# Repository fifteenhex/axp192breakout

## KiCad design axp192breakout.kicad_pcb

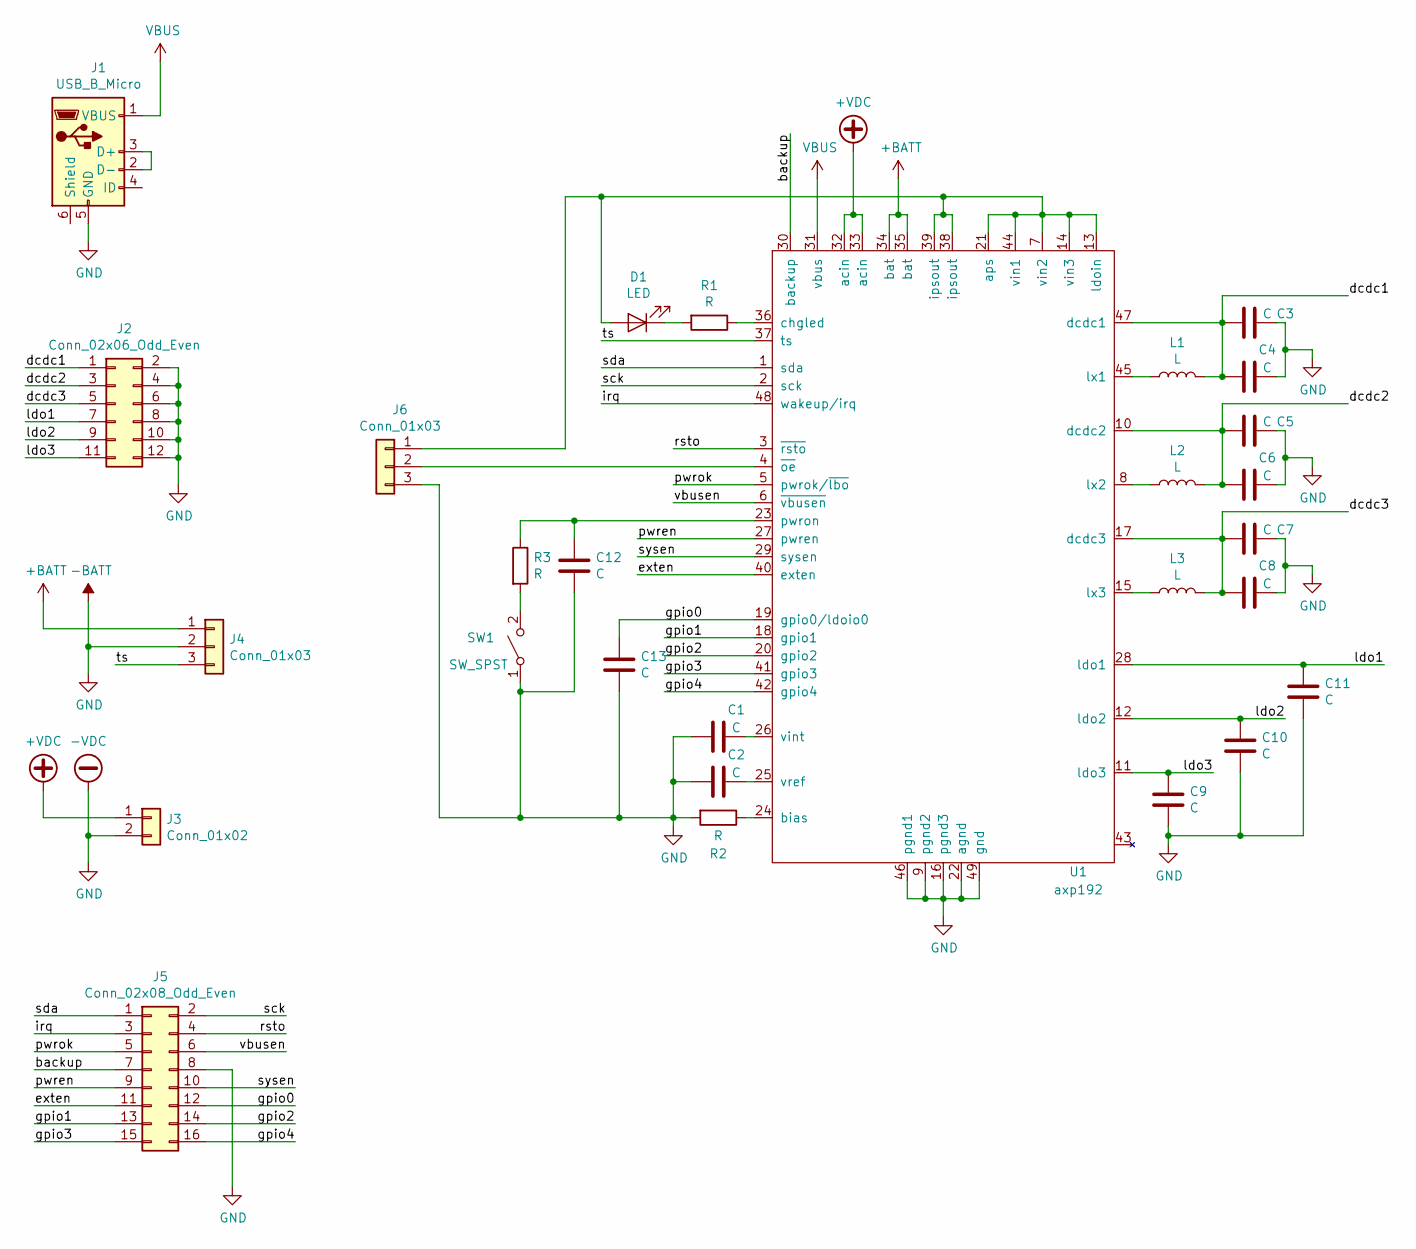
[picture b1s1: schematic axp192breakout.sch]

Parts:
C1, C2, C3, C4, C5, C6, C7, C8, C9, C10, C11, C12, C13: C; C_0402_1005Metric
D1: LED; LED_0603_1608Metric
J1: USB_B_Micro; USB-MICRO-B
J2: Conn_02x06_Odd_Even; PinHeader_2x06_P2.54mm_Vertical
J3: Conn_01x02; PinHeader_2x01_P2.54mm_Vertical
J4: Conn_01x03; PinHeader_1x03_P2.54mm_Vertical
J5: Conn_02x08_Odd_Even; PinHeader_2x08_P2.54mm_Vertical
J6: Conn_01x03; PinSocket_1x03_P2.54mm_Vertical
L1, L2, L3: L; L_Taiyo-Yuden_MD-2020
R1, R2, R3: R; R_0402_1005Metric
SW1: SW_SPST; PinSocket_1x02_P2.54mm_Vertical
U1: axp192; QFN-48-1EP_6x6mm_P0.4mm_EP4.2x4.2mm_ThermalVias

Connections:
+BATT: J4.1, U1.34 (bat), U1.35 (bat)
+VDC: J3.1, U1.32 (acin), U1.33 (acin)
-BATT: C1.2, C2.2, C3.1, C4.1, C5.1, C6.1, C7.1, C8.1, C9.2, C10.2, C11.2, C12.2, C13.2, J1.5 (GND), J2.2, J2.4, J2.6, J2.8, J2.10, J2.12, J3.2, J4.2, J5.8, J6.3, R2.2, SW1.1 (A), U1.9 (pgnd2), U1.16 (pgnd3), U1.22 (agnd), U1.46 (pgnd1), U1.49 (gnd)
/backup: J5.7, U1.30 (backup)
/dcdc1: C3.2, C4.2, J2.1, L1.2, U1.47 (dcdc1)
/dcdc2: C5.2, C6.2, J2.3, L2.2, U1.10 (dcdc2)
/dcdc3: C7.2, C8.2, J2.5, L3.2, U1.17 (dcdc3)
/exten: J5.11, U1.40 (exten)
/gpio0: C13.1, J5.12, U1.19 (gpio0/ldoio0)
/gpio1: J5.13, U1.18 (gpio1)
/gpio2: J5.14, U1.20 (gpio2)
/gpio3: J5.15, U1.41 (gpio3)
/gpio4: J5.16, U1.42 (gpio4)
/irq: J5.3, U1.48 (wakeup/irq)
/ldo1: C11.1, J2.7, U1.28 (ldo1)
/ldo2: C10.1, J2.9, U1.12 (ldo2)
/ldo3: C9.1, J2.11, U1.11 (ldo3)
/pwren: J5.9, U1.27 (pwren)
/pwrok: J5.5, U1.5 (pwrok/~lbo)
/rsto: J5.4, U1.3 (~rsto)
/sck: J5.2, U1.2 (sck)
/sda: J5.1, U1.1 (sda)
/sysen: J5.10, U1.29 (sysen)
/ts: J4.3, U1.37 (ts)
/vbusen: J5.6, U1.6 (~vbusen)
unnamed: C1.1, U1.26 (vint)
unnamed: C2.1, U1.25 (vref)
unnamed: C12.1, R3.1, U1.23 (pwron)
unnamed: D1.1 (K), R1.2
unnamed: D1.2 (A), J6.1, U1.7 (vin2), U1.13 (ldoin), U1.14 (vin3), U1.21 (aps), U1.38 (ipsout), U1.39 (ipsout), U1.44 (vin1)
unnamed: J1.2 (D-), J1.3 (D+)
unnamed: J6.2, U1.4 (~oe)
unnamed: L1.1, U1.45 (lx1)
unnamed: L2.1, U1.8 (lx2)
unnamed: L3.1, U1.15 (lx3)
unnamed: R1.1, U1.36 (chgled)
unnamed: R2.1, U1.24 (bias)
unnamed: R3.2, SW1.2 (B)
VBUS: J1.1 (VBUS), U1.31 (vbus)

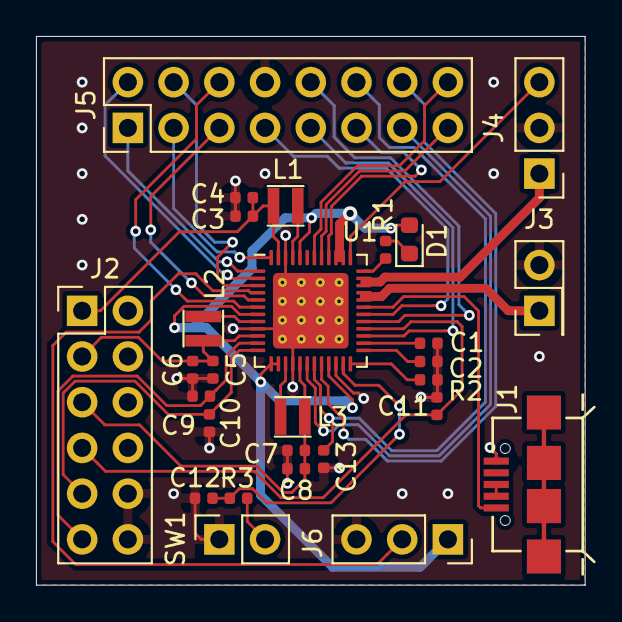
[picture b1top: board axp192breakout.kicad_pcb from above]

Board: 2 copper layers, 30.5 x 30.5 mm, 28 parts (0 on the bottom side), 39 nets.

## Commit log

2019-09-03 rev0
2019-09-03 Add datasheet for AXP192
2019-09-03 Fix soldermask. Add rendered gerbers. Add rendered schematic.
2019-09-03 Add missing drill file
